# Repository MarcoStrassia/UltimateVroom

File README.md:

# UltimateVroom

UltimateVroom is a dual-motor brushless controller for a Boosted Board V1. Marco and I are building it to replace the dead stock ESC.

It runs from a 12S A123 26650 pack, which is 39.6 V nominal and 43.2 V charged, and drives two motors. An STM32F103 does the control, IRS2104 gate drivers switch CSD19532 FETs, and the board is 4 layers.

## Newest board: `MotorController-V3/`

The newest board is in the `MotorController-V3/` folder (added 2026-11-10). Start with `MotorController-V3/README.md`: it says which file to open, what has been checked, and what is still wrong with it. Short version: it is a new 4-layer design around an STM32G474 and DRV8300 drivers, it is routed and passes KiCad's checks, and it is not ready to order because it is still bigger than the stock ESC.

To get the files without using git: click the green **Code** button on the GitHub page, then **Download ZIP**.

## Earlier board: `MotorController-Rebuild/`

Everything below describes the earlier board.

The KiCad project is in `MotorController-Rebuild/`. GitHub doesn't render KiCad files, so clone the repo and open `MotorController-Rebuild/MotorController-Rebuild.kicad_pro` in KiCad 10. `MotorController-Rebuild/docs/` has our spec PDF, design notes, and notes and photos of the stock ESC. `MotorController-Rebuild/review/current/previews/` has images of the board and a PDF of the schematic. `earlier-schematic/` is Marco's first schematic.

The board is routed. ERC has 0 errors and 7 warnings (four-way junctions). DRC has 0 errors and 0 unconnected items, and the schematic matches the board.

Still open: motor current limits, a thermal check, firmware, the Bluetooth remote, and fitting the board into the Boosted V1 ESC footprint, which is about 84 x 100 mm with six phase pads.

Patrick Liu and Marco Strassia, UCSB

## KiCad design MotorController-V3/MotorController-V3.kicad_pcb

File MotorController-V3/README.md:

# MotorController-V3

This is the newest board (layout finished 2026-11-13). It is a new design, not an edit of `MotorController-Rebuild/`.

It is a 4-layer dual-motor FOC controller for the Boosted Board V1: one STM32G474, two DRV8300 gate drivers, twelve 100 V MOSFETs, low-side current sensing on every phase, and hall inputs for both motors.

**The layout is finished at its current size: it is fully routed, passes KiCad's checks, and every high-current path now meets the 13 A copper target. It still does not fit the stock ESC footprint**, so it is a bench board, not a drop-in. That and the smaller open items are under "Known problems".

## How to open it

1. On the GitHub page, click the green **Code** button, then **Download ZIP**, and unzip it. (Or `git pull` if you already cloned the repo.)
2. Install KiCad 10 if you don't have it.
3. Open `MotorController-V3/MotorController-V3.kicad_pro`. That opens the project; from there open the schematic and the PCB.

If you just want to look without installing anything, open the files in `previews/`:

| File | What it is |
|---|---|
| `previews/schematic.pdf` | The whole schematic |
| `previews/board-top.png`, `board-bottom.png` | 3D renders of both sides |
| `previews/layer-F.Cu.svg`, `layer-In1.Cu.svg`, `layer-In2.Cu.svg`, `layer-B.Cu.svg` | Each copper layer (open in a browser) |

## What is on it

| Part | Choice |
|---|---|
| MCU | STM32G474RET6, LQFP-64, 24 MHz crystal |
| Gate drivers | 2 x DRV8300UDPWR, one per motor |
| MOSFETs | 12 x SiR512DP (100 V, PowerPAK SO-8) |
| Current sense | 2 mOhm low-side shunt on every phase into INA240A1 amplifiers |
| Supplies | LM5164 buck to 12 V for the gate drivers, AP63203 buck to 3.3 V, TLV803E reset supervisor |
| Input | 40 A 72 VDC fuse, SMCJ48A TVS, 2 x 1500 uF 80 V bulk caps lying flat |
| Connections | Flat solder pads for battery and the six motor phases, one 5-pin JST-SH hall connector per motor, SWD header, UART header, three status LEDs, test points on the PWM lines |

Layers: top = parts and signals, In1 = ground plane, In2 = battery bus plane (3.3 V plane under the MCU), bottom = phase pours and signals. Outer copper is planned as 2 oz, inner as 1 oz. All parts are on the top side.

The board is sized for a 12S A123 pack (43.2 V charged) and about 13 A continuous, 30 A burst per motor.

## What changed on 2026-11-13

- The six half-bridges were re-rowed so each phase pad sits next to its FET pair. Phase current now runs on top and bottom copper in parallel and no longer squeezes past the shunt ground vias.
- Every signal was routed again after that move. The PWM lines run as two ordered buses on the bottom layer (motor 1 north-west from the MCU, motor 2 west under the MCU), so they reach the gate drivers in pin order without crossing.
- Layer changes on signal nets went from 62 to 14, vias from 814 to 513, track segments from 1696 to 1254.
- All routing is at 0, 45 or 90 degrees. The earlier version had 41 any-angle segments.
- Small part moves: the motor 2 phase A sense filter cap (C45) now sits at the MCU pin, the hall A pull-up (R56) sits next to its series resistor, R57/R58 are turned around, the PWM and brake test points are grouped next to the gate drivers and the MCU, and the U5 sense amplifier is wired like U6 and U7 so its ground pin is no longer boxed in.
- The schematic only changed in three footprint names (the flat solder pads now carry stitching holes).

## What has been checked

- KiCad DRC with schematic parity, zones refilled: 0 errors, 0 warnings, 0 unconnected, schematic and board match.
- KiCad ERC: 0 errors. 31 warnings (wire ends off grid, and library symbols that differ from the copies in the schematic), the same as before.
- Copper width on every high-current path against 13 A continuous, 10 C rise (IPC-2221, 2 oz outer and 1 oz inner copper). Every FET, shunt and connector now gets at least 13 A. The table is under "Copper widths" below.
- Gate drive: all 12 gate traces run next to their return, the longest is 32.0 mm of track (25.8 mm pad to pad).
- No signal track cuts a phase, bus or ground pour into two pieces.
- Gerbers, drill files, the position file and the BOM export from KiCad without errors.

Nothing here has been built or powered. No person has reviewed the layout yet.

### Copper widths

Narrowest point of each path and what the path carries with its layers in parallel:

| Net | Narrowest copper | Weakest part gets |
|---|---|---|
| Battery bus (VBUS) | 5.0 mm top, plus the In2 plane | 14.6 A (Q9) |
| Ground return | 2.75 mm bottom plus 8.25 mm on In1 | 13.8 A (R32) |
| Battery input (VBAT) | 13.0 mm top, 11.5 mm bottom | 48.6 A (fuse) |
| Motor 1 phase A / B / C | 5.25 mm top (A also 5.5 mm bottom) | 20.8 / 13.2 / 13.2 A |
| Motor 2 phase A / B / C | 5.0 mm top plus 5.5 mm bottom / 5.25 mm / 5.25 mm | 20.3 / 13.2 / 13.2 A |
| Low-side nodes A / B / C (both motors) | 5.0 mm top + 4.0 mm bottom / 3.5 + 3.75 mm / 5.0 + 4.25 mm | 18.4 / 13.6 / 18.4 A |

The previous version had four phase paths between 8.8 and 12.2 A and a battery bus estimate of 4.5 A per FET by the same rule. The margins on phases B and C (13.2 A) and on ground (13.8 A) are thin. They meet the rule, they do not beat it by much.

## Known problems

**1. It is too big and the mounting holes are in the wrong place.** This is the one thing that still stops it being a drop-in board.
The board is 92.4 x 100 mm with holes on a roughly 84 x 70 mm pattern. Measured from photos of a real V1 ESC, the stock board is about 74 x 85 mm with screws about 67.6 x 59 mm apart. Those photo numbers are good to about 1 mm, so the real board needs calipers: outline width and height, each screw centre from one corner, and the hole diameter. The size did not change in this update. Fitting the stock outline means laying the board out again.

**2. Signal runs inside the inner planes.**
To keep signals from cutting the phase and ground pours on the bottom, some of them run on the inner layers, always north-south so they sit along the current flow instead of across it:

- In the battery bus plane (In2): the three motor 1 hall lines and a +3V3 feed along the west edge (about 30 mm and 42 mm), the two phase A low-side gate traces (27 mm each), two short +12V crossings and two short +3V3 crossings.
- In the 3.3 V plane under the MCU (In2): the three motor 2 low-side PWM taps to their test points (10 mm each) and 8 mm of the reset line.
- In the ground plane (In1): the two phase B low-side gate traces, 15.5 mm each.
- The rest of the In2 routing (reset, motor 1 phase A/B current sense, motor 2 brake input, one +3V3 feed) is in the area north of the MCU where In2 has no plane, so it cuts nothing.

That is more inner-layer track than the previous version (about 215 mm in the bus plane against 123 mm, plus the two gate traces in the ground plane, which are new). The bus and ground still pass the copper check with these slots in place, but a cleaner board would keep In1 unbroken. The root cause is unchanged: the MCU pins were assigned before the parts were placed, so motor 1 and motor 2 PWM, sense and hall pins are interleaved around the package.

**3. Gate traces are long.**
Re-rowing the FETs moved some of them away from their driver. The longest gate trace is now 32.0 mm (phase C high side, both motors), against 17.3 mm before. Each one runs beside its return, and the limit set for this layout was 26 mm pad to pad and 33 mm of track, which holds. Gate resistor values should be checked on the bench for ringing.

**4. Bootstrap caps for phase B.**
The return side of C13 and C26 reaches its phase node through an 18 mm, 0.2 mm wide trace. It works electrically, but it should be shortened in the next layout.

**5. Current sense inputs share the ground net.**
Every INA240 IN- pin is on the GND net in the schematic. The layout keeps each IN- trace on its own path to the shunt pad (no vias or pours touching it away from the shunt), but a cleaner fix is to give each IN- its own net with a net tie at the shunt.

**6. Things to know before writing firmware.**
- UART TX is on PB11 and RX on PA3. That pair is LPUART1, not USART2.
- The two motors use the two advanced timers, TIM1 and TIM8. The pin map is in the schematic; check it against the datasheet before relying on it.
- There is no Bluetooth module on this board. The UART header is the only link for a remote.

**7. Small things.**
- R1's reference label is on the fabrication layer, not the silkscreen. There was no free spot for it between the phase pads.
- UART RX still changes layers twice more than it needs to.

**8. Not checked at all.**
Thermal behaviour, the fuse against two 30 A bursts, gate resistor values against ringing, the bootstrap and dead-time settings, and whether the flat bulk caps and the heatsink fit the enclosure.

## What is next

Measure the stock ESC with calipers, then redo the layout at the real size with the MCU pins assigned after placement, so the PWM, sense and hall lines leave the MCU in the order the drivers need and the inner planes can stay unbroken.

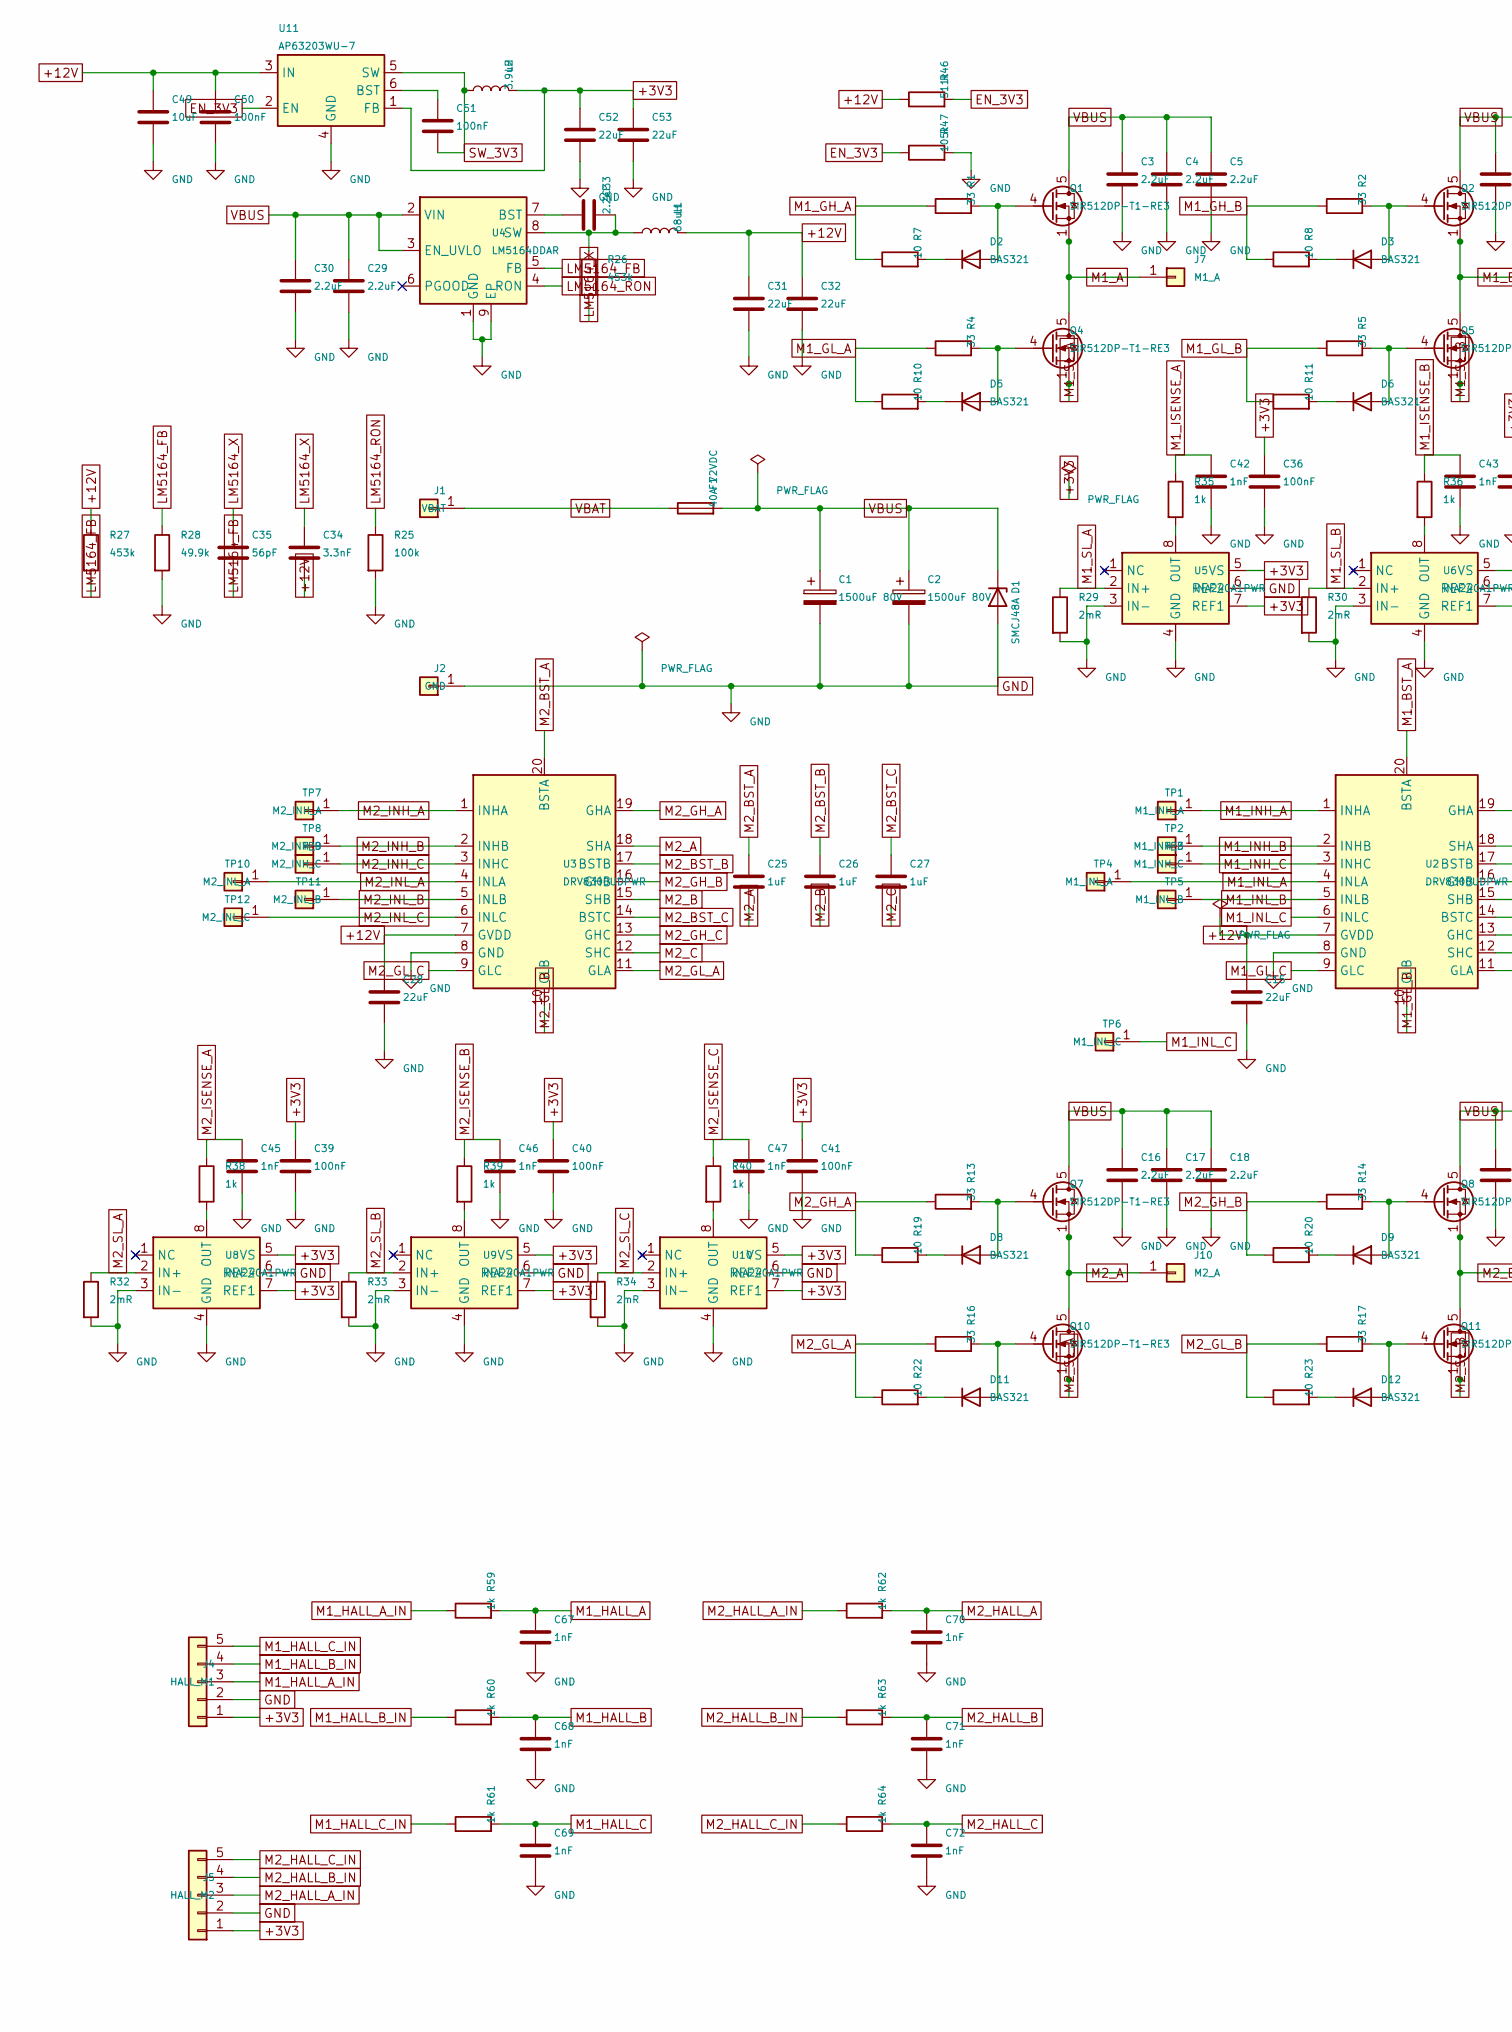
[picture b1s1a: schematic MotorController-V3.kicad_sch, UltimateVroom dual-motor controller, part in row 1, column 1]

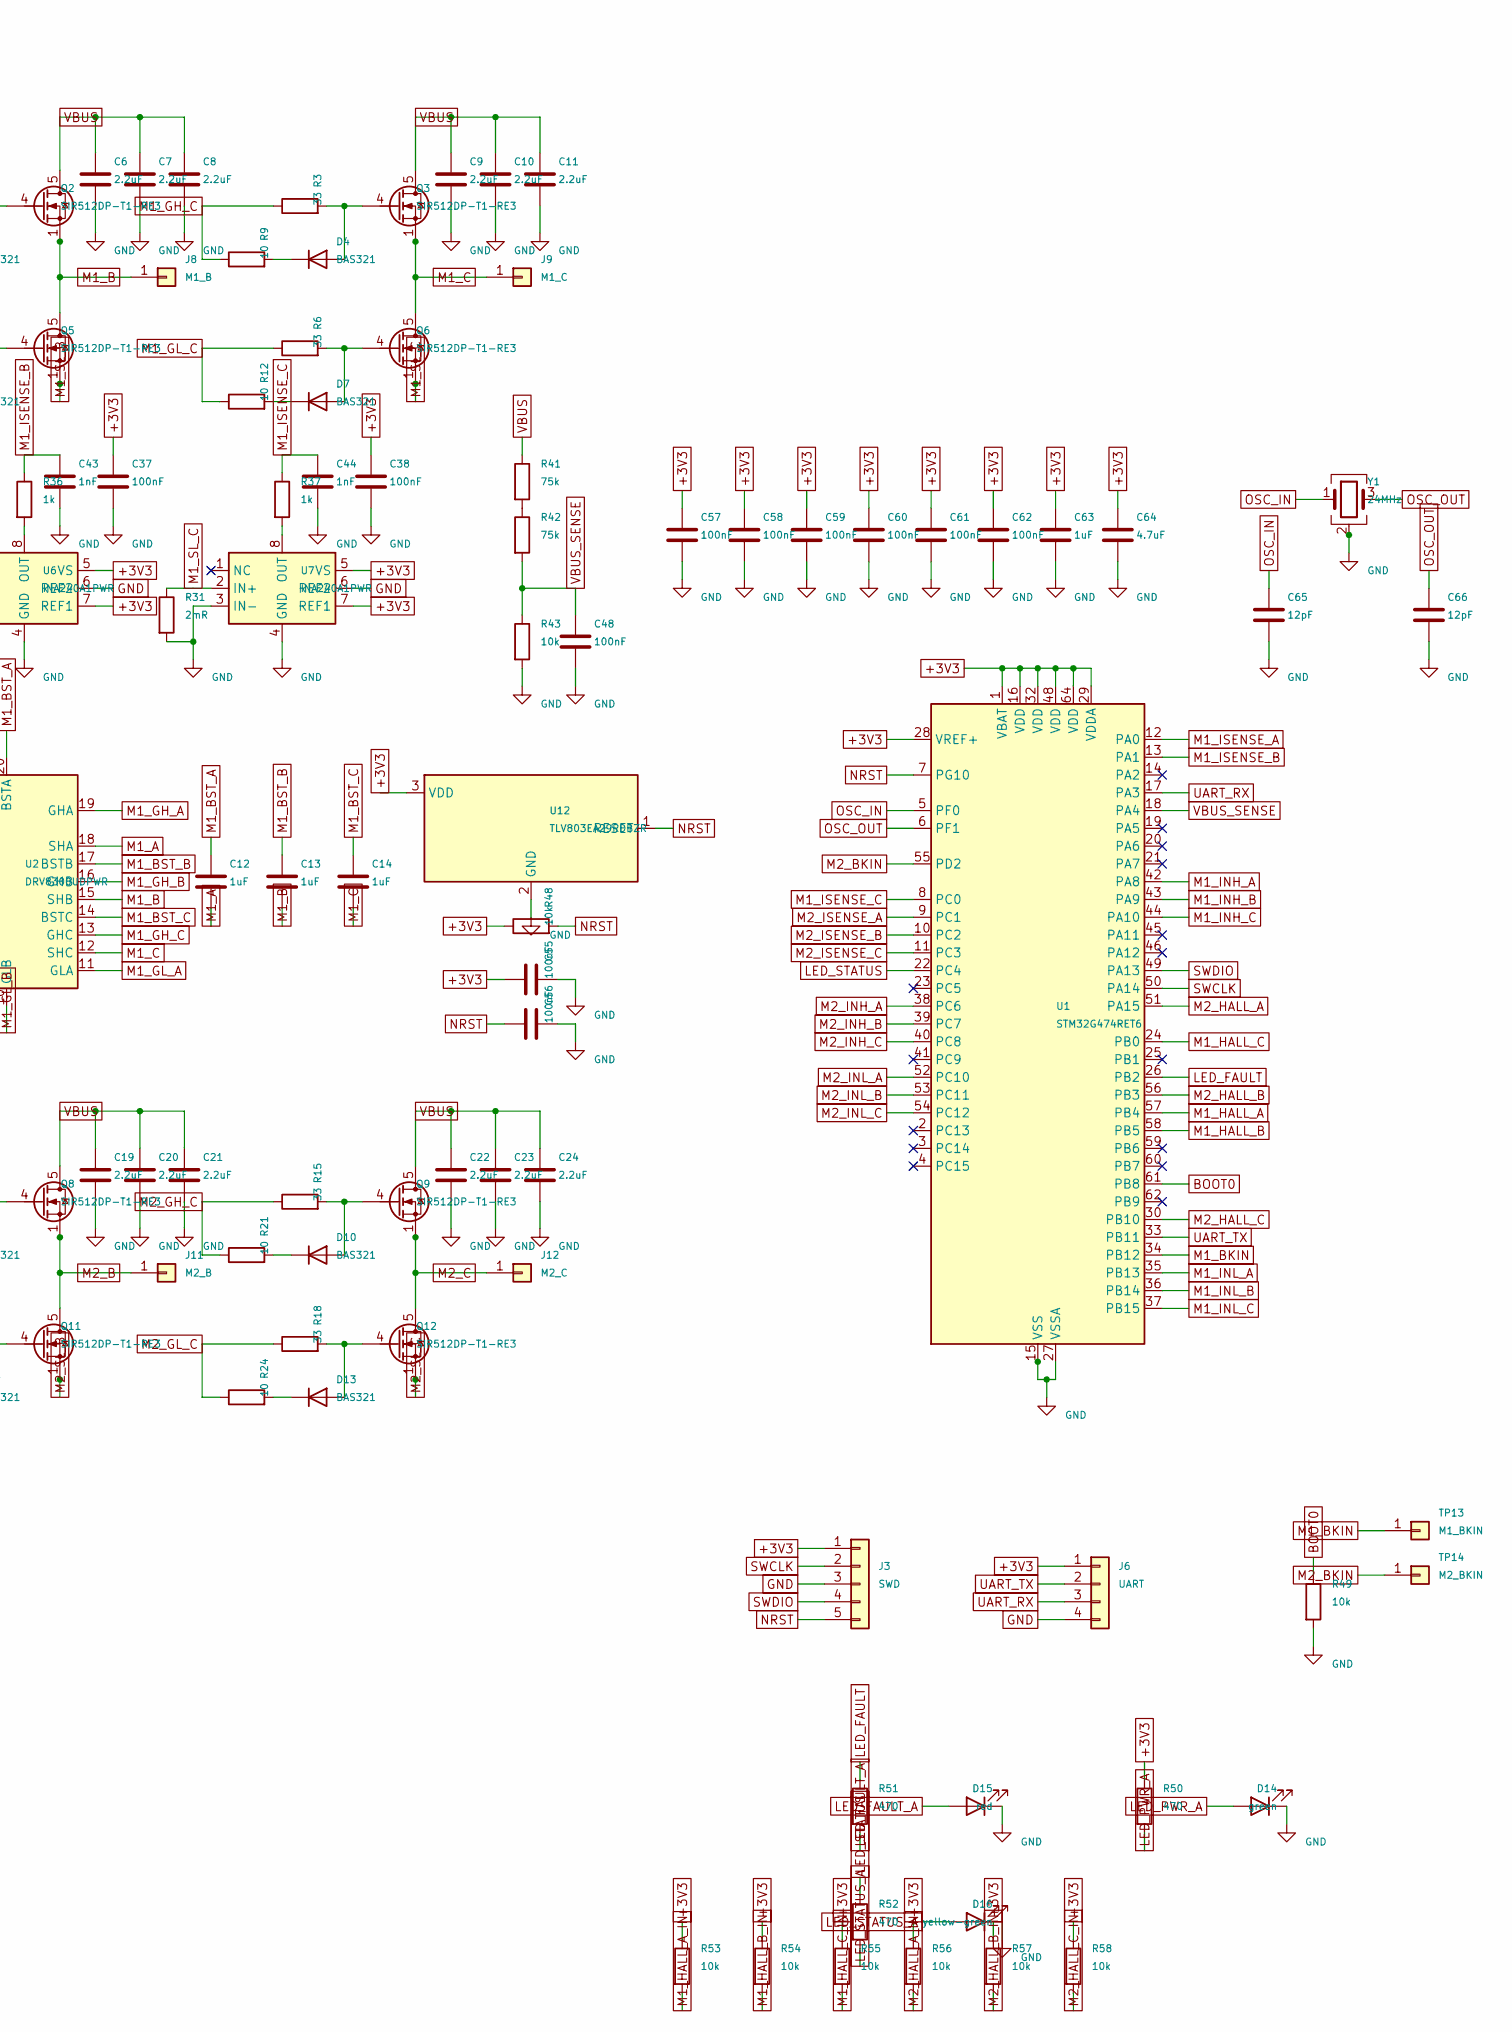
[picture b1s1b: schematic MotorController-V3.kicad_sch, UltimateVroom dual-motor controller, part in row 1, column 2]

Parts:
C1, C2: 1500uF 80V; CP_Radial_D18.0mm_L40.0mm_P7.50mm_Horizontal; MPN 80ZLH1500MEFC18X40
C3, C4, C5, C6, C7, C8, C9, C10, C11, C16, C17, C18, C19, C20, C21, C22, C23, C24, C29, C30: 2.2uF; C_1210_3225Metric; MPN CGA6N3X7R2A225KT0Y0U
C12, C13, C14, C25, C26, C27: 1uF; C_0603_1608Metric; MPN CL10B105KA8NFNC
C15, C28: 22uF; C_0805_2012Metric; MPN CL21A226MAQNNNE
C31, C32: 22uF; C_1210_3225Metric; MPN TMK325B7226KMHP
C33: 2.2nF; C_0402_1005Metric; MPN CC0402KRX7R9BB222
C34: 3.3nF; C_0402_1005Metric; MPN CC0402KRX7R8BB332
C35: 56pF; C_0402_1005Metric; MPN CC0402JRNPO9BN560
C36, C37, C38, C39, C40, C41, C48, C50, C51, C55, C56, C57, C58, C59, C60, C61, C62: 100nF; C_0603_1608Metric; MPN CC0603KRX7R9BB104
C42, C43, C44, C45, C46, C47, C67, C68, C69, C70, C71, C72: 1nF; C_0603_1608Metric; MPN CC0603JRNPO9BN102
C49: 10uF; C_0805_2012Metric; MPN CL21A106KAYNNNE
C52, C53: 22uF; C_0805_2012Metric; MPN CL21A226MPQNNNE
C63: 1uF; C_0603_1608Metric; MPN CL10A105KB8NNNC
C64: 4.7uF; C_0603_1608Metric; MPN CL10A475KO8NNNC
C65, C66: 12pF; C_0603_1608Metric; MPN CL10C120JB8NNNC
D1: SMCJ48A; D_SMC; MPN SMCJ48A
D2, D3, D4, D5, D6, D7, D8, D9, D10, D11, D12, D13: BAS321; D_SOD-323; MPN BAS321,115
D14: green; LED_0603_1608Metric; MPN SML-310MTT86
D15: red; LED_0603_1608Metric; MPN SML-D12V1WT86
D16: yellow-green; LED_0603_1608Metric; MPN SML-D13FWT86C
F1: 40A 72VDC; Fuse_Eaton_1025HC_40-50A_L12.4mm_W4.5mm; MPN 0456040.DR
J1: VBAT; SolderPad_SMD_6.0x10.0mm_10Via
J2: GND; SolderPad_SMD_6.0x10.0mm_10Via
J3: SWD; PinHeader_1x05_P2.54mm_Vertical; MPN 61300511121
J4: HALL_M1; JST_SH_SM05B-SRSS-TB_1x05-1MP_P1.00mm_Horizontal; MPN SM05B-SRSS-TB(LF)(SN)
J5: HALL_M2; JST_SH_SM05B-SRSS-TB_1x05-1MP_P1.00mm_Horizontal; MPN SM05B-SRSS-TB(LF)(SN)
J6: UART; PinHeader_1x04_P2.54mm_Vertical; MPN 77311-462K04LF
J7: M1_A; SolderPad_SMD_6.0x10.0mm_10Via
J8: M1_B; SolderPad_SMD_6.0x10.0mm_10Via
J9: M1_C; SolderPad_SMD_6.0x10.0mm_10Via
J10: M2_A; SolderPad_SMD_6.0x10.0mm_10Via
J11: M2_B; SolderPad_SMD_6.0x10.0mm_10Via
J12: M2_C; SolderPad_SMD_6.0x10.0mm_10Via
L1: 68uH; L_Bourns_SRP1245A; MPN NS12575T680MN
L2: 3.9uH; L_Bourns-SRN6028; MPN SRN6028C-3R9M
Q1, Q2, Q3, Q4, Q5, Q6, Q7, Q8, Q9, Q10, Q11, Q12: SIR512DP-T1-RE3; PowerPAK_SO-8_Single; MPN SIR512DP-T1-RE3
R1, R2, R3, R4, R5, R6, R13, R14, R15, R16, R17, R18: 33; R_0603_1608Metric; MPN RC0603FR-0733RL
R7, R8, R9, R10, R11, R12, R19, R20, R21, R22, R23, R24: 10; R_0603_1608Metric; MPN CRCW060310R0FKEA
R25: 100k; R_0603_1608Metric; MPN RC0603FR-07100KL
R26, R27: 453k; R_0603_1608Metric; MPN RC0603FR-07453KL
R28: 49.9k; R_0603_1608Metric; MPN RC0603FR-0749K9L
R29, R30, R31, R32, R33, R34: 2mR; R_2512_6332Metric; MPN PA2512FKE7T0R002E
R35, R36, R37, R38, R39, R40, R59, R60, R61, R62, R63, R64: 1k; R_0603_1608Metric; MPN RC0603JR-071KL
R41, R42: 75k; R_0603_1608Metric; MPN RC0603FR-0775KL
R43, R48, R49, R53, R54, R55, R56, R57, R58: 10k; R_0603_1608Metric; MPN RC0603FR-0710KL
R46: 511k; R_0603_1608Metric; MPN AC0603FR-07511KL
R47: 105k; R_0603_1608Metric; MPN RC0603FR-07105KL
R50, R51, R52: 470; R_0603_1608Metric; MPN RC0603FR-07470RL
TP1: M1_INH_A; TestPoint_Pad_D1.5mm
TP2: M1_INH_B; TestPoint_Pad_D1.5mm
TP3: M1_INH_C; TestPoint_Pad_D1.5mm
TP4: M1_INL_A; TestPoint_Pad_D1.5mm
TP5: M1_INL_B; TestPoint_Pad_D1.5mm
TP6: M1_INL_C; TestPoint_Pad_D1.5mm
TP7: M2_INH_A; TestPoint_Pad_D1.5mm
TP8: M2_INH_B; TestPoint_Pad_D1.5mm
TP9: M2_INH_C; TestPoint_Pad_D1.5mm
TP10: M2_INL_A; TestPoint_Pad_D1.5mm
TP11: M2_INL_B; TestPoint_Pad_D1.5mm
TP12: M2_INL_C; TestPoint_Pad_D1.5mm
TP13: M1_BKIN; TestPoint_Pad_D1.5mm
TP14: M2_BKIN; TestPoint_Pad_D1.5mm
U1: STM32G474RET6; LQFP-64_10x10mm_P0.5mm; MPN STM32G474RET6
U2, U3: DRV8300UDPWR; TSSOP-20_4.4x6.5mm_P0.65mm; MPN DRV8300UDPWR
U4: LM5164DDAR; Texas_HTSOP-8-1EP_3.9x4.9mm_P1.27mm_EP2.95x4.9mm_Mask2.4x3.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; MPN LM5164DDAR
U5, U6, U7, U8, U9, U10: INA240A1PWR; TSSOP-8_4.4x3mm_P0.65mm; MPN INA240A1PWR
U11: AP63203WU-7; TSOT-23-6; MPN AP63203WU-7
U12: TLV803EA29RDBZR; SOT-23; MPN TLV803EA29RDBZR
Y1: 24MHz; Crystal_SMD_3225-4Pin_3.2x2.5mm; MPN K3A240001010

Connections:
+3V3: C36.1, C37.1, C38.1, C39.1, C40.1, C41.1, C52.1, C53.1, C55.1, C57.1, C58.1, C59.1, C60.1, C61.1, C62.1, C63.1, C64.1, J3.1, J4.1, J5.1, J6.1, L2.2, R48.1, R50.1, R53.1, R54.1, R55.1, R56.1, R57.1, R58.1, U1.1 (VBAT), U1.16 (VDD), U1.28 (VREF+), U1.29 (VDDA), U1.32 (VDD), U1.48 (VDD), U1.64 (VDD), U5.5 (VS), U5.7 (REF1), U6.5 (VS), U6.7 (REF1), U7.5 (VS), U7.7 (REF1), U8.5 (VS), U8.7 (REF1), U9.5 (VS), U9.7 (REF1), U10.5 (VS), U10.7 (REF1), U11.1 (FB), U12.3 (VDD)
+12V: C15.1, C28.1, C31.1, C32.1, C34.2, C49.1, C50.1, L1.2, R27.1, R46.1, U2.7 (GVDD), U3.7 (GVDD), U11.3 (IN)
BOOT0: R49.1, U1.61 (PB8)
EN_3V3: R46.2, R47.1, U11.2 (EN)
GND: C1.2, C2.2, C3.2, C4.2, C5.2, C6.2, C7.2, C8.2, C9.2, C10.2, C11.2, C15.2, C16.2, C17.2, C18.2, C19.2, C20.2, C21.2, C22.2, C23.2, C24.2, C28.2, C29.2, C30.2, C31.2, C32.2, C36.2, C37.2, C38.2, C39.2, C40.2, C41.2, C42.2, C43.2, C44.2, C45.2, C46.2, C47.2, C48.2, C49.2, C50.2, C52.2, C53.2, C55.2, C56.2, C57.2, C58.2, C59.2, C60.2, C61.2, C62.2, C63.2, C64.2, C65.2, C66.2, C67.2, C68.2, C69.2, C70.2, C71.2, C72.2, D1.2 (A), D14.1 (K), D15.1 (K), D16.1 (K), J2.1, J3.3, J4.2, J5.2, J6.4, R25.2, R28.2, R29.2, R30.2, R31.2, R32.2, R33.2, R34.2, R43.2, R47.2, R49.2, U1.15 (VSS), U1.27 (VSSA), U1.31 (VSS), U1.47 (VSS), U1.63 (VSS), U2.8 (GND), U3.8 (GND), U4.1 (GND), U4.9 (EP), U5.3 (IN-), U5.4 (GND), U5.6 (REF2), U6.3 (IN-), U6.4 (GND), U6.6 (REF2), U7.3 (IN-), U7.4 (GND), U7.6 (REF2), U8.3 (IN-), U8.4 (GND), U8.6 (REF2), U9.3 (IN-), U9.4 (GND), U9.6 (REF2), U10.3 (IN-), U10.4 (GND), U10.6 (REF2), U11.4 (GND), U12.2 (GND), Y1.2 (G), Y1.4 (G)
LED_FAULT: R51.1, U1.26 (PB2)
LED_FAULT_A: D15.2 (A), R51.2
LED_PWR_A: D14.2 (A), R50.2
LED_STATUS: R52.1, U1.22 (PC4)
LED_STATUS_A: D16.2 (A), R52.2
LM5164_FB: C35.2, R27.2, R28.1, U4.5 (FB)
LM5164_RON: R25.1, U4.4 (RON)
LM5164_X: C34.1, C35.1, R26.2
M1_A: C12.2, J7.1, Q1.1 (S), Q1.2 (S), Q1.3 (S), Q4.5 (D), U2.18 (SHA)
M1_B: C13.2, J8.1, Q2.1 (S), Q2.2 (S), Q2.3 (S), Q5.5 (D), U2.15 (SHB)
M1_BKIN: TP13.1, U1.34 (PB12)
M1_BST_A: C12.1, U2.20 (BSTA)
M1_BST_B: C13.1, U2.17 (BSTB)
M1_BST_C: C14.1, U2.14 (BSTC)
M1_C: C14.2, J9.1, Q3.1 (S), Q3.2 (S), Q3.3 (S), Q6.5 (D), U2.12 (SHC)
M1_GH_A: R1.1, R7.1, U2.19 (GHA)
M1_GH_B: R2.1, R8.1, U2.16 (GHB)
M1_GH_C: R3.1, R9.1, U2.13 (GHC)
M1_GL_A: R4.1, R10.1, U2.11 (GLA)
M1_GL_B: R5.1, R11.1, U2.10 (GLB)
M1_GL_C: R6.1, R12.1, U2.9 (GLC)
M1_HALL_A: C67.1, R59.2, U1.57 (PB4)
M1_HALL_A_IN: J4.3, R53.2, R59.1
M1_HALL_B: C68.1, R60.2, U1.58 (PB5)
M1_HALL_B_IN: J4.4, R54.2, R60.1
M1_HALL_C: C69.1, R61.2, U1.24 (PB0)
M1_HALL_C_IN: J4.5, R55.2, R61.1
M1_INH_A: TP1.1, U1.42 (PA8), U2.1 (INHA)
M1_INH_B: TP2.1, U1.43 (PA9), U2.2 (INHB)
M1_INH_C: TP3.1, U1.44 (PA10), U2.3 (INHC)
M1_INL_A: TP4.1, U1.35 (PB13), U2.4 (INLA)
M1_INL_B: TP5.1, U1.36 (PB14), U2.5 (INLB)
M1_INL_C: TP6.1, U1.37 (PB15), U2.6 (INLC)
M1_ISENSE_A: C42.1, R35.1, U1.12 (PA0)
M1_ISENSE_B: C43.1, R36.1, U1.13 (PA1)
M1_ISENSE_C: C44.1, R37.1, U1.8 (PC0)
M1_SL_A: Q4.1 (S), Q4.2 (S), Q4.3 (S), R29.1, U5.2 (IN+)
M1_SL_B: Q5.1 (S), Q5.2 (S), Q5.3 (S), R30.1, U6.2 (IN+)
M1_SL_C: Q6.1 (S), Q6.2 (S), Q6.3 (S), R31.1, U7.2 (IN+)
M2_A: C25.2, J10.1, Q7.1 (S), Q7.2 (S), Q7.3 (S), Q10.5 (D), U3.18 (SHA)
M2_B: C26.2, J11.1, Q8.1 (S), Q8.2 (S), Q8.3 (S), Q11.5 (D), U3.15 (SHB)
M2_BKIN: TP14.1, U1.55 (PD2)
M2_BST_A: C25.1, U3.20 (BSTA)
M2_BST_B: C26.1, U3.17 (BSTB)
M2_BST_C: C27.1, U3.14 (BSTC)
M2_C: C27.2, J12.1, Q9.1 (S), Q9.2 (S), Q9.3 (S), Q12.5 (D), U3.12 (SHC)
M2_GH_A: R13.1, R19.1, U3.19 (GHA)
M2_GH_B: R14.1, R20.1, U3.16 (GHB)
M2_GH_C: R15.1, R21.1, U3.13 (GHC)
M2_GL_A: R16.1, R22.1, U3.11 (GLA)
M2_GL_B: R17.1, R23.1, U3.10 (GLB)
M2_GL_C: R18.1, R24.1, U3.9 (GLC)
M2_HALL_A: C70.1, R62.2, U1.51 (PA15)
M2_HALL_A_IN: J5.3, R56.2, R62.1
M2_HALL_B: C71.1, R63.2, U1.56 (PB3)
M2_HALL_B_IN: J5.4, R57.2, R63.1
M2_HALL_C: C72.1, R64.2, U1.30 (PB10)
M2_HALL_C_IN: J5.5, R58.2, R64.1
M2_INH_A: TP7.1, U1.38 (PC6), U3.1 (INHA)
M2_INH_B: TP8.1, U1.39 (PC7), U3.2 (INHB)
M2_INH_C: TP9.1, U1.40 (PC8), U3.3 (INHC)
M2_INL_A: TP10.1, U1.52 (PC10), U3.4 (INLA)
M2_INL_B: TP11.1, U1.53 (PC11), U3.5 (INLB)
M2_INL_C: TP12.1, U1.54 (PC12), U3.6 (INLC)
M2_ISENSE_A: C45.1, R38.1, U1.9 (PC1)
M2_ISENSE_B: C46.1, R39.1, U1.10 (PC2)
M2_ISENSE_C: C47.1, R40.1, U1.11 (PC3)
M2_SL_A: Q10.1 (S), Q10.2 (S), Q10.3 (S), R32.1, U8.2 (IN+)
M2_SL_B: Q11.1 (S), Q11.2 (S), Q11.3 (S), R33.1, U9.2 (IN+)
M2_SL_C: Q12.1 (S), Q12.2 (S), Q12.3 (S), R34.1, U10.2 (IN+)
NRST: C56.1, J3.5, R48.2, U1.7 (PG10), U12.1 (RESET)
unnamed: D2.2 (A), Q1.4 (G), R1.2
unnamed: D2.1 (K), R7.2
unnamed: D3.2 (A), Q2.4 (G), R2.2
unnamed: D3.1 (K), R8.2
unnamed: D4.2 (A), Q3.4 (G), R3.2
unnamed: D4.1 (K), R9.2
unnamed: D5.2 (A), Q4.4 (G), R4.2
unnamed: D5.1 (K), R10.2
unnamed: D6.2 (A), Q5.4 (G), R5.2
unnamed: D6.1 (K), R11.2
unnamed: D7.2 (A), Q6.4 (G), R6.2
unnamed: D7.1 (K), R12.2
unnamed: D8.2 (A), Q7.4 (G), R13.2
unnamed: D8.1 (K), R19.2
unnamed: D9.2 (A), Q8.4 (G), R14.2
unnamed: D9.1 (K), R20.2
unnamed: D10.2 (A), Q9.4 (G), R15.2
unnamed: D10.1 (K), R21.2
unnamed: D11.2 (A), Q10.4 (G), R16.2
unnamed: D11.1 (K), R22.2
unnamed: D12.2 (A), Q11.4 (G), R17.2
unnamed: D12.1 (K), R23.2
unnamed: D13.2 (A), Q12.4 (G), R18.2
unnamed: D13.1 (K), R24.2
unnamed: R41.2, R42.1
unnamed: C33.1, U4.7 (BST)
unnamed: C33.2, L1.1, R26.1, U4.8 (SW)
unnamed: R35.2, U5.8 (OUT)
unnamed: R36.2, U6.8 (OUT)
unnamed: R37.2, U7.8 (OUT)
unnamed: R38.2, U8.8 (OUT)
unnamed: R39.2, U9.8 (OUT)
unnamed: R40.2, U10.8 (OUT)
unnamed: C51.1, U11.6 (BST)
OSC_IN: C65.1, U1.5 (PF0), Y1.1
OSC_OUT: C66.1, U1.6 (PF1), Y1.3
SWCLK: J3.2, U1.50 (PA14)
SWDIO: J3.4, U1.49 (PA13)
SW_3V3: C51.2, L2.1, U11.5 (SW)
UART_RX: J6.3, U1.17 (PA3)
UART_TX: J6.2, U1.33 (PB11)
VBAT: F1.1, J1.1
VBUS: C1.1, C2.1, C3.1, C4.1, C5.1, C6.1, C7.1, C8.1, C9.1, C10.1, C11.1, C16.1, C17.1, C18.1, C19.1, C20.1, C21.1, C22.1, C23.1, C24.1, C29.1, C30.1, D1.1 (K), F1.2, Q1.5 (D), Q2.5 (D), Q3.5 (D), Q7.5 (D), Q8.5 (D), Q9.5 (D), R41.1, U4.2 (VIN), U4.3 (EN_UVLO)
VBUS_SENSE: C48.1, R42.2, R43.1, U1.18 (PA4)

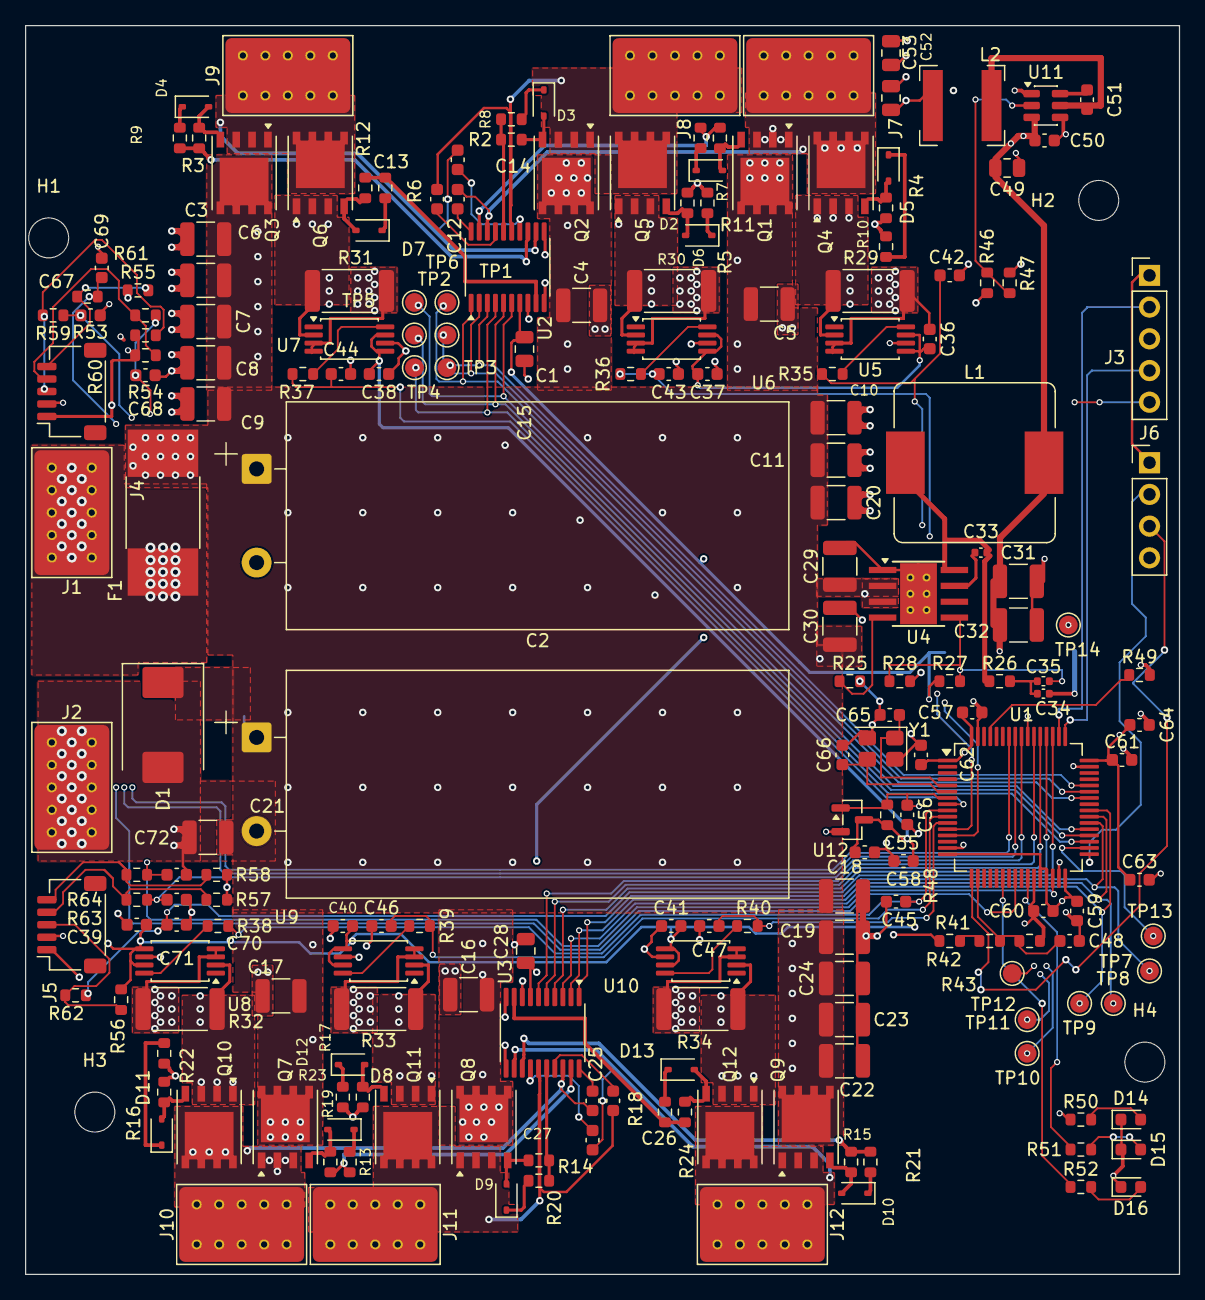
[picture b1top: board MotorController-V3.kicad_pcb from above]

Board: 4 copper layers, 92.4 x 100.0 mm, 207 parts (0 on the bottom side), 120 nets.

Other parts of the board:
H1, H2, H3, H4: MountingHole_3.2mm_M3

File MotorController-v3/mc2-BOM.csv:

"Refs","Value","Footprint","MPN","Manufacturer","Qty"
"C1,C2","1500uF 80V","Wright:CP_Radial_D18.0mm_L40.0mm_P7.50mm_Horizontal","80ZLH1500MEFC18X40","Rubycon","2"
"C3,C4,C5,C6,C7,C8,C9,C10,C11,C16,C17,C18,C19,C20,C21,C22,C23,C24,C29,C30","2.2uF","Capacitor_SMD:C_1210_3225Metric","CGA6N3X7R2A225KT0Y0U","TDK","20"
"C12,C13,C14,C25,C26,C27","1uF","Capacitor_SMD:C_0603_1608Metric","CL10B105KA8NFNC","Samsung Electro Mechanics","6"
"C15,C28","22uF","Capacitor_SMD:C_0805_2012Metric","CL21A226MAQNNNE","Samsung Electro Mechanics","2"
"C31,C32","22uF","Capacitor_SMD:C_1210_3225Metric","TMK325B7226KMHP","Taiyo Yuden","2"
"C33","2.2nF","Capacitor_SMD:C_0402_1005Metric","CC0402KRX7R9BB222","YAGEO","1"
"C34","3.3nF","Capacitor_SMD:C_0402_1005Metric","CC0402KRX7R8BB332","YAGEO","1"
"C35","56pF","Capacitor_SMD:C_0402_1005Metric","CC0402JRNPO9BN560","YAGEO","1"
"C36,C37,C38,C39,C40,C41,C48,C50,C51,C55,C56,C57,C58,C59,C60,C61,C62","100nF","Capacitor_SMD:C_0603_1608Metric","CC0603KRX7R9BB104","YAGEO","17"
"C42,C43,C44,C45,C46,C47,C67,C68,C69,C70,C71,C72","1nF","Capacitor_SMD:C_0603_1608Metric","CC0603JRNPO9BN102","YAGEO","12"
"C49","10uF","Capacitor_SMD:C_0805_2012Metric","CL21A106KAYNNNE","Samsung Electro Mechanics","1"
"C52,C53","22uF","Capacitor_SMD:C_0805_2012Metric","CL21A226MPQNNNE","Samsung Electro Mechanics","2"
"C54","56pF","Capacitor_SMD:C_0402_1005Metric","CC0402GRNPO9BN560","YAGEO","1"
"C63","1uF","Capacitor_SMD:C_0603_1608Metric","CL10A105KB8NNNC","Samsung Electro Mechanics","1"
"C64","4.7uF","Capacitor_SMD:C_0603_1608Metric","CL10A475KO8NNNC","Samsung Electro Mechanics","1"
"C65,C66","12pF","Capacitor_SMD:C_0603_1608Metric","CL10C120JB8NNNC","Samsung Electro Mechanics","2"
"D1","SMCJ48A","Diode_SMD:D_SMC","SMCJ48A","Littelfuse","1"
"D2,D3,D4,D5,D6,D7,D8,D9,D10,D11,D12,D13","BAS321","Diode_SMD:D_SOD-323","BAS321,115","Nexperia","12"
"D14","green","LED_SMD:LED_0603_1608Metric","SML-310MTT86","ROHM Semicon","1"
"D15","red","LED_SMD:LED_0603_1608Metric","SML-D12V1WT86","ROHM Semicon","1"
"D16","yellow-green","LED_SMD:LED_0603_1608Metric","SML-D13FWT86C","ROHM Semicon","1"
"F1","40A 72VDC","Wright:Fuse_Eaton_1025HC_40-50A_L12.4mm_W4.5mm","0456040.DR","Littelfuse","1"
"J1","VBAT","Wright:SolderPad_SMD_6.0x10.0mm_10Via","","","1"
"J2","GND","Wright:SolderPad_SMD_6.0x10.0mm_10Via","","","1"
"J3","SWD","Connector_PinHeader_2.54mm:PinHeader_1x05_P2.54mm_Vertical","61300511121","Wurth Elektronik","1"
"J4","HALL_M1","Connector_JST:JST_SH_SM05B-SRSS-TB_1x05-1MP_P1.00mm_Horizontal","SM05B-SRSS-TB(LF)(SN)","JST","1"
"J5","HALL_M2","Connector_JST:JST_SH_SM05B-SRSS-TB_1x05-1MP_P1.00mm_Horizontal","SM05B-SRSS-TB(LF)(SN)","JST","1"
"J6","UART","Connector_PinHeader_2.54mm:PinHeader_1x04_P2.54mm_Vertical","77311-462K04LF","Amphenol ICC","1"
"J7","M1_A","Wright:SolderPad_SMD_6.0x10.0mm_10Via","","","1"
"J8","M1_B","Wright:SolderPad_SMD_6.0x10.0mm_10Via","","","1"
"J9","M1_C","Wright:SolderPad_SMD_6.0x10.0mm_10Via","","","1"
"J10","M2_A","Wright:SolderPad_SMD_6.0x10.0mm_10Via","","","1"
"J11","M2_B","Wright:SolderPad_SMD_6.0x10.0mm_10Via","","","1"
"J12","M2_C","Wright:SolderPad_SMD_6.0x10.0mm_10Via","","","1"
"L1","68uH","Inductor_SMD:L_Bourns_SRP1245A","NS12575T680MN","Taiyo Yuden","1"
"L2","3.9uH","Inductor_SMD:L_Bourns-SRN6028","SRN6028C-3R9M","BOURNS","1"
"Q1,Q2,Q3,Q4,Q5,Q6,Q7,Q8,Q9,Q10,Q11,Q12","SIR512DP-T1-RE3","Package_SO:PowerPAK_SO-8_Single","SIR512DP-T1-RE3","Vishay Intertech","12"
"R1,R2,R3,R4,R5,R6,R13,R14,R15,R16,R17,R18","33","Resistor_SMD:R_0603_1608Metric","RC0603FR-0733RL","YAGEO","12"
"R7,R8,R9,R10,R11,R12,R19,R20,R21,R22,R23,R24","10","Resistor_SMD:R_0603_1608Metric","CRCW060310R0FKEA","Vishay Intertech","12"
"R25,R44","100k","Resistor_SMD:R_0603_1608Metric","RC0603FR-07100KL","YAGEO","2"
"R26,R27","453k","Resistor_SMD:R_0603_1608Metric","RC0603FR-07453KL","YAGEO","2"
"R28","49.9k","Resistor_SMD:R_0603_1608Metric","RC0603FR-0749K9L","YAGEO","1"
"R29,R30,R31,R32,R33,R34","2mR","Resistor_SMD:R_2512_6332Metric","PA2512FKE7T0R002E","YAGEO","6"
"R35,R36,R37,R38,R39,R40,R59,R60,R61,R62,R63,R64","1k","Resistor_SMD:R_0603_1608Metric","RC0603JR-071KL","YAGEO","12"
"R41,R42","75k","Resistor_SMD:R_0603_1608Metric","RC0603FR-0775KL","YAGEO","2"
"R43,R48,R49,R53,R54,R55,R56,R57,R58","10k","Resistor_SMD:R_0603_1608Metric","RC0603FR-0710KL","YAGEO","9"
"R45","22.1k","Resistor_SMD:R_0603_1608Metric","RC0603FR-0722K1L","YAGEO","1"
"R46","511k","Resistor_SMD:R_0603_1608Metric","AC0603FR-07511KL","YAGEO","1"
"R47","105k","Resistor_SMD:R_0603_1608Metric","RC0603FR-07105KL","YAGEO","1"
"R50,R51,R52","470","Resistor_SMD:R_0603_1608Metric","RC0603FR-07470RL","YAGEO","3"
"TP1","M1_INH_A","TestPoint:TestPoint_Pad_D1.5mm","","","1"
"TP2","M1_INH_B","TestPoint:TestPoint_Pad_D1.5mm","","","1"
"TP3","M1_INH_C","TestPoint:TestPoint_Pad_D1.5mm","","","1"
"TP4","M1_INL_A","TestPoint:TestPoint_Pad_D1.5mm","","","1"
"TP5","M1_INL_B","TestPoint:TestPoint_Pad_D1.5mm","","","1"
"TP6","M1_INL_C","TestPoint:TestPoint_Pad_D1.5mm","","","1"
"TP7","M2_INH_A","TestPoint:TestPoint_Pad_D1.5mm","","","1"
"TP8","M2_INH_B","TestPoint:TestPoint_Pad_D1.5mm","","","1"
"TP9","M2_INH_C","TestPoint:TestPoint_Pad_D1.5mm","","","1"
"TP10","M2_INL_A","TestPoint:TestPoint_Pad_D1.5mm","","","1"
"TP11","M2_INL_B","TestPoint:TestPoint_Pad_D1.5mm","","","1"
"TP12","M2_INL_C","TestPoint:TestPoint_Pad_D1.5mm","","","1"
"TP13","M1_BKIN","TestPoint:TestPoint_Pad_D1.5mm","","","1"
"TP14","M2_BKIN","TestPoint:TestPoint_Pad_D1.5mm","","","1"
"U1","STM32G474RET6","Package_QFP:LQFP-64_10x10mm_P0.5mm","STM32G474RET6","STMicroelectronics","1"
"U2,U3","DRV8300UDPWR","Package_SO:TSSOP-20_4.4x6.5mm_P0.65mm","DRV8300UDPWR","Texas Instruments","2"
"U4","LM5164DDAR","Package_SO:Texas_HTSOP-8-1EP_3.9x4.9mm_P1.27mm_EP2.95x4.9mm_Mask2.4x3.1mm_ThermalVias","LM5164DDAR","Texas Instruments","1"
"U5,U6,U7,U8,U9,U10","INA240A1PWR","Package_SO:TSSOP-8_4.4x3mm_P0.65mm","INA240A1PWR","Texas Instruments","6"
"U11","AP63203WU-7","Package_TO_SOT_SMD:SOT-23-6","AP63203WU-7","Diodes Incorporated","1"
"U12","TLV803EA29RDBZR","Package_TO_SOT_SMD:SOT-23","TLV803EA29RDBZR","Texas Instruments","1"
"Y1","24MHz","Crystal:Crystal_SMD_3225-4Pin_3.2x2.5mm","K3A240001010","KYX","1"
"C73","CC0603KRX7R9BB104","","CC0603KRX7R9BB104","YAGEO","1"
"C74","CC0603KRX7R9BB104","","CC0603KRX7R9BB104","YAGEO","1"
"C75","CL21A106KAYNNNE","","CL21A106KAYNNNE","Samsung Electro Mechanics","1"
"C76","CC0603KRX7R9BB104","","CC0603KRX7R9BB104","YAGEO","1"
